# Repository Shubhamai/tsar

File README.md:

# Tsar

This repository contains Tsar flight computer that I have been developing for autonomous vehicles. The goal is to build a general-purpose & fully programmable flight computer that can be used for any autonomous model vehicles. The design is intended to be modular, cost-effective, and easy to manufacture.

The PCB is designed in KiCad and updated to version 8.0.3.

## Version History

### V3 [Latest Version]

The design is very similar to V2 but with different IO style and no pyro channels. The secondary chip is STM32G0 for a lower number of components. The design is still in progress.

#### Key Features:
- Main Dual core ESP32-S3
- Secondary STM32G0 as an IO extender
- 2.4GHz SX1280 radio
- Ublox-M10S GNSS
- BMI088 IMU (up to ± 24 g, ± 2000°/s)
- BMP390 barometer (up to 10KM), MMC5983MA magnetometer for heading
- SD card and flash (ESP32-S3 inbuilt) for data logging & storage
- 14 PWM channels (combined 3A)
- ~20 auxiliary outputs with SPI, I2C, analog, digital pins, etc.
- 6-16V power input, (reverse+over+under)-voltage, over-current protection
- Dimensions: 40mm width, 82mm height

### V2 [April 2024]

With learnings from V1, V2 was designed to be more cost-effective, less complex, and easier to manufacture. The BOM cost was around $60-80, and the board had 4 layers. With a trace width and minimum clearance of 0.2mm, QFN chips, and 0603 components, it was easier to manufacture and assemble. The board was manufactured and partially tested but not yet used in flight.

#### Key Features:
- Main Dual core ESP32-S3
- Secondary RP2040 as an IO extender
- 2.4GHz SX1280 radio
- Ublox-M10S GNSS
- BMI088 IMU (up to ± 24 g, ± 2000°/s)
- BMP390 barometer (up to 10KM), MMC5983MA magnetometer for heading
- 4 pyro channels (up to 16V, 4A) with continuity
- SD card and flash (ESP32-S3 inbuilt) for data logging & storage
- 14 PWM channels (combined 3A)
- 17 auxiliary outputs with SPI, I2C, analog, digital pins, etc.
- 6-16V power input, (reverse+over+under)-voltage, over-current protection
- Dimensions: 40mm width, 82mm height

### V1 [March 2024]

The first attempt at designing a flight computer. The design was powerful, using Teensy, but highly complex and less cost-effective. The BOM cost was around $120-150, and the board had 4 layers. With a trace width and minimum clearance of 0.127mm, BGA chips, and 0402 components, it was challenging to manufacture and assemble. This version was never manufactured or tested.

#### Key Features:
- Main Chip: NXP IMXRT106DVJ6B (Teensy 4.1)
- RP2040 as an IO extender
- 2.4GHz SX1280 radio
- Ublox-M10S GNSS
- BMI088 IMU (up to ± 24 g, ± 2000°/s)
- BMP390 barometer (up to 10KM), MMC5983MA magnetometer for heading
- 4 pyro channels (up to 16V, 4A) with continuity
- SD card and flash for data logging & storage
- 14 PWM channels (combined 3A)
- 30 auxiliary outputs with SPI, I2C, analog, digital pins, etc.
- 6-16V power input, (reverse+over+under)-voltage, over-current protection
- Dimensions: 50mm width, 100mm height

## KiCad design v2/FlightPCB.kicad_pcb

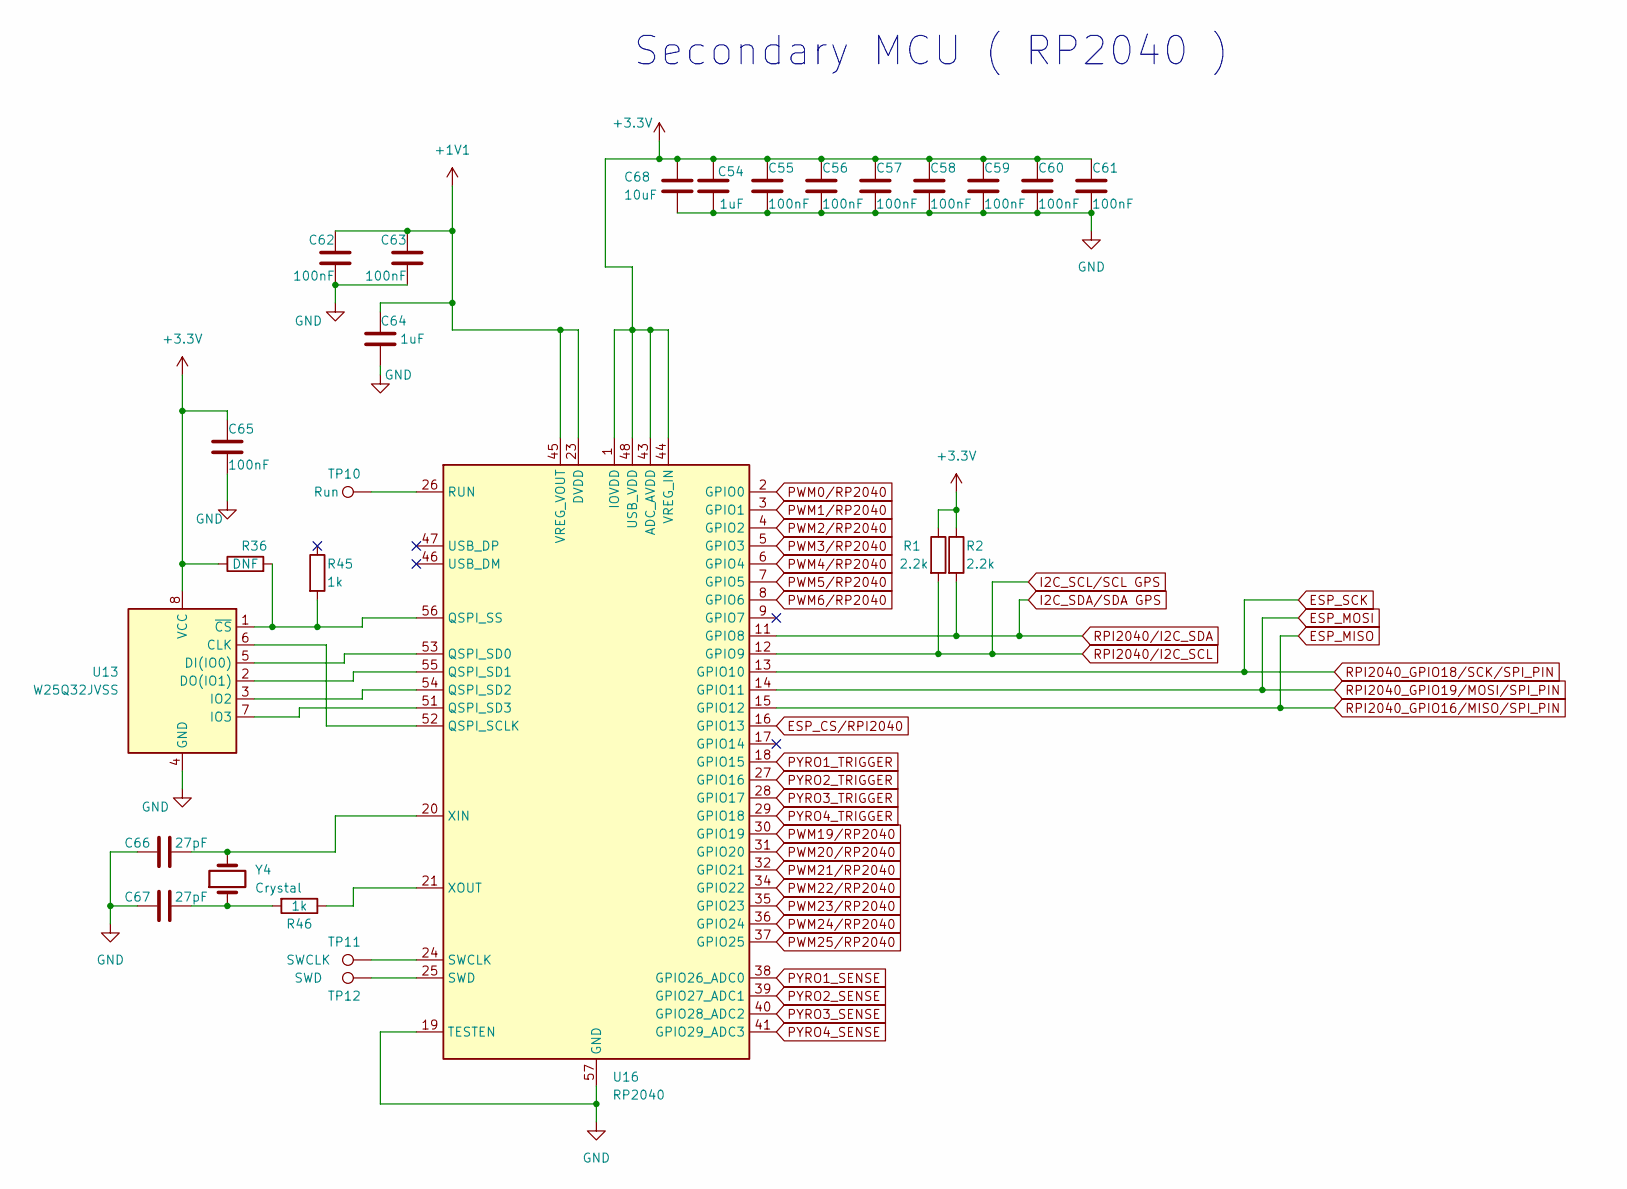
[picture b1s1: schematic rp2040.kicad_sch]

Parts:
C54, C64: 1uF; C_0603_1608Metric
C55, C56, C57, C58, C59, C60, C61, C62, C63, C65: 100nF; C_0603_1608Metric
C66, C67: 27pF; C_0603_1608Metric
C68: 10uF; C_0603_1608Metric
R1, R2: 2.2k; R_0603_1608Metric
R36: DNF; R_0402_1005Metric
R45, R46: 1k; R_0402_1005Metric
TP10: Run; TestPoint_Pad_D1.0mm
TP11: SWCLK; TestPoint_Pad_D2.0mm
TP12: SWD; TestPoint_Pad_D2.0mm
U13: W25Q32JVSS; SOIC-8_5.23x5.23mm_P1.27mm
U16: RP2040; QFN-56-1EP_7x7mm_P0.4mm_EP4x4mm
Y4: Crystal; Crystal_SMD_Abracon_ABM8G-4Pin_3.2x2.5mm

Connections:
+1V1: C62.1, C63.1, C64.1, U16.23 (DVDD), U16.45 (VREG_VOUT), U16.50 (DVDD)
+3.3V: C54.1, C55.1, C56.1, C57.1, C58.1, C59.1, C60.1, C61.1, C65.1, C68.1, R1.1, R2.1, R36.1, U13.8 (VCC), U16.1 (IOVDD), U16.10 (IOVDD), U16.22 (IOVDD), U16.33 (IOVDD), U16.42 (IOVDD), U16.43 (ADC_AVDD), U16.44 (VREG_IN), U16.48 (USB_VDD), U16.49 (IOVDD); also elsewhere on the board
BARO_MISO: U16.15 (GPIO12); also elsewhere on the board
BARO_MOSI: U16.14 (GPIO11); also elsewhere on the board
BARO_SCK: U16.13 (GPIO10); also elsewhere on the board
ESP_CS/RPI2040: U16.16 (GPIO13); also elsewhere on the board
ESP_SCL: R1.2, U16.12 (GPIO9); also elsewhere on the board
ESP_SDA: R2.2, U16.11 (GPIO8); also elsewhere on the board
GND: C54.2, C55.2, C56.2, C57.2, C58.2, C59.2, C60.2, C61.2, C62.2, C63.2, C64.2, C65.2, C66.1, C67.2, C68.2, U13.4 (GND), U16.19 (TESTEN), U16.57 (GND); also elsewhere on the board
unnamed: C67.1, R46.2, Y4.1
unnamed: U13.6 (CLK), U16.52 (QSPI_SCLK)
unnamed: U13.5 (DI(IO0)), U16.53 (QSPI_SD0)
unnamed: U13.2 (DO(IO1)), U16.55 (QSPI_SD1)
unnamed: U13.3 (IO2), U16.54 (QSPI_SD2)
unnamed: U13.7 (IO3), U16.51 (QSPI_SD3)
unnamed: R36.2, R45.2, U13.1 (~CS), U16.56 (QSPI_SS)
unnamed: TP10.1, U16.26 (RUN)
unnamed: TP11.1, U16.24 (SWCLK)
unnamed: TP12.1, U16.25 (SWD)
unnamed: C66.2, U16.20 (XIN), Y4.2
unnamed: R46.1, U16.21 (XOUT)
PWM0/RP2040: U16.2 (GPIO0); also elsewhere on the board
PWM1/RP2040: U16.3 (GPIO1); also elsewhere on the board
PWM2/RP2040: U16.4 (GPIO2); also elsewhere on the board
PWM3/RP2040: U16.5 (GPIO3); also elsewhere on the board
PWM4/RP2040: U16.6 (GPIO4); also elsewhere on the board
PWM5/RP2040: U16.7 (GPIO5); also elsewhere on the board
PWM6/RP2040: U16.8 (GPIO6); also elsewhere on the board
PWM19/RP2040: U16.30 (GPIO19); also elsewhere on the board
PWM20/RP2040: U16.31 (GPIO20); also elsewhere on the board
PWM21/RP2040: U16.32 (GPIO21); also elsewhere on the board
PWM22/RP2040: U16.34 (GPIO22); also elsewhere on the board
PWM23/RP2040: U16.35 (GPIO23); also elsewhere on the board
PWM24/RP2040: U16.36 (GPIO24); also elsewhere on the board
PWM25/RP2040: U16.37 (GPIO25); also elsewhere on the board
PYRO1_SENSE: U16.38 (GPIO26_ADC0); also elsewhere on the board
PYRO1_TRIGGER: U16.18 (GPIO15); also elsewhere on the board
PYRO2_SENSE: U16.39 (GPIO27_ADC1); also elsewhere on the board
PYRO2_TRIGGER: U16.27 (GPIO16); also elsewhere on the board
PYRO3_SENSE: U16.40 (GPIO28_ADC2); also elsewhere on the board
PYRO3_TRIGGER: U16.28 (GPIO17); also elsewhere on the board
PYRO4_SENSE: U16.41 (GPIO29_ADC3); also elsewhere on the board
PYRO4_TRIGGER: U16.29 (GPIO18); also elsewhere on the board

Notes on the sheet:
Secondary MCU ( RP2040 )

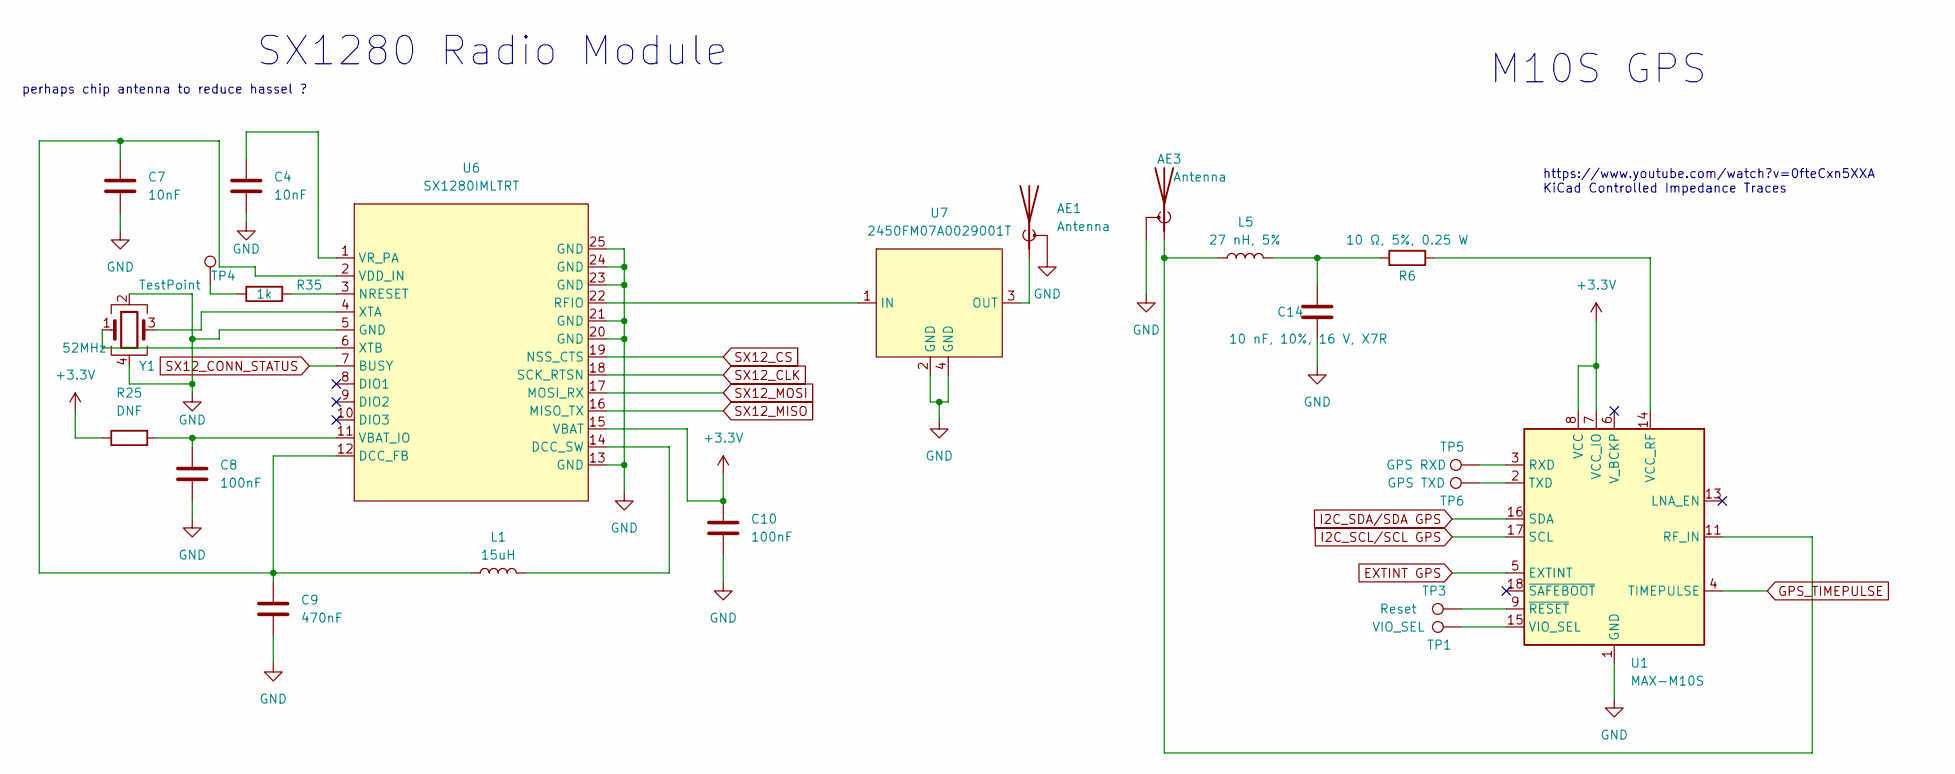
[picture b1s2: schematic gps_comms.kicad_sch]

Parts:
AE1, AE3: Antenna; SMA_Amphenol_901-144_Vertical
C4, C7: 10nF; C_0603_1608Metric
C8, C10: 100nF; C_0603_1608Metric
C9: 470nF; C_0402_1005Metric
C14: 10 nF, 10%, 16 V, X7R; C_0603_1608Metric
L1: 15uH; L_0805_2012Metric
L5: 27 nH, 5%; L_0402_1005Metric
R6: 10 Ω, 5%, 0.25 W; R_0402_1005Metric
R25: DNF; R_0402_1005Metric
R35: 1k; R_0402_1005Metric
TP1: VIO_SEL; TestPoint_Pad_D1.0mm
TP3: Reset; TestPoint_Pad_D1.0mm
TP4: TestPoint; TestPoint_Pad_D1.0mm
TP5: GPS RXD; TestPoint_Pad_D1.0mm
TP6: GPS TXD; TestPoint_Pad_D1.0mm
U1: MAX-M10S; ublox_MAX
U6: SX1280IMLTRT; QFN-24-1EP_4x4mm_P0.5mm_EP2.7x2.7mm
U7: 2450FM07A0029001T
Y1: 52MHz; Crystal_SMD_2016-4Pin_2.0x1.6mm

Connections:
+3.3V: C10.1, R25.1, U1.7 (VCC_IO), U1.8 (VCC), U6.15 (VBAT); also elsewhere on the board
BARO_MISO: U6.16 (MISO_TX); also elsewhere on the board
BARO_MOSI: U6.17 (MOSI_RX); also elsewhere on the board
BARO_SCK: U6.18 (SCK_RTSN); also elsewhere on the board
ESP_SCL: U1.17 (SCL); also elsewhere on the board
ESP_SDA: U1.16 (SDA); also elsewhere on the board
EXTINT GPS: U1.5 (EXTINT); also elsewhere on the board
GND: AE1.2 (Shield), AE3.2 (Shield), C4.2, C7.2, C8.2, C9.2, C10.2, C14.1, U1.1 (GND), U1.10 (GND), U1.12 (GND), U6.5 (GND), U6.13 (GND), U6.20 (GND), U6.21 (GND), U6.23 (GND), U6.24 (GND), U6.25 (GND), U7.2 (GND), U7.4 (GND), Y1.2, Y1.4; also elsewhere on the board
GPS_TIMEPULSE: U1.4 (TIMEPULSE); also elsewhere on the board
unnamed: AE1.1 (A), U7.3 (OUT)
unnamed: AE3.1 (A), L5.1, U1.11 (RF_IN)
unnamed: C14.2, L5.2, R6.1
unnamed: R35.1, TP4.1
unnamed: TP5.1, U1.3 (RXD)
unnamed: TP6.1, U1.2 (TXD)
unnamed: R6.2, U1.14 (VCC_RF)
unnamed: TP1.1, U1.15 (VIO_SEL)
unnamed: TP3.1, U1.9 (~RESET)
unnamed: C7.1, C9.1, L1.1, U6.2 (VDD_IN), U6.12 (DCC_FB)
unnamed: L1.2, U6.14 (DCC_SW)
unnamed: R35.2, U6.3 (NRESET)
unnamed: U6.22 (RFIO), U7.1 (IN)
unnamed: C8.1, R25.2, U6.11 (VBAT_IO)
unnamed: C4.1, U6.1 (VR_PA)
unnamed: U6.4 (XTA), Y1.3
unnamed: U6.6 (XTB), Y1.1
SX12_CONN_STATUS: U6.7 (BUSY); also elsewhere on the board
SX12_CS: U6.19 (NSS_CTS); also elsewhere on the board

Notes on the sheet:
perhaps chip antenna to reduce hassel ?
https://www.youtube.com/watch?v=0fteCxn5XXA KiCad Controlled Impedance Traces
M10S GPS
SX1280 Radio Module

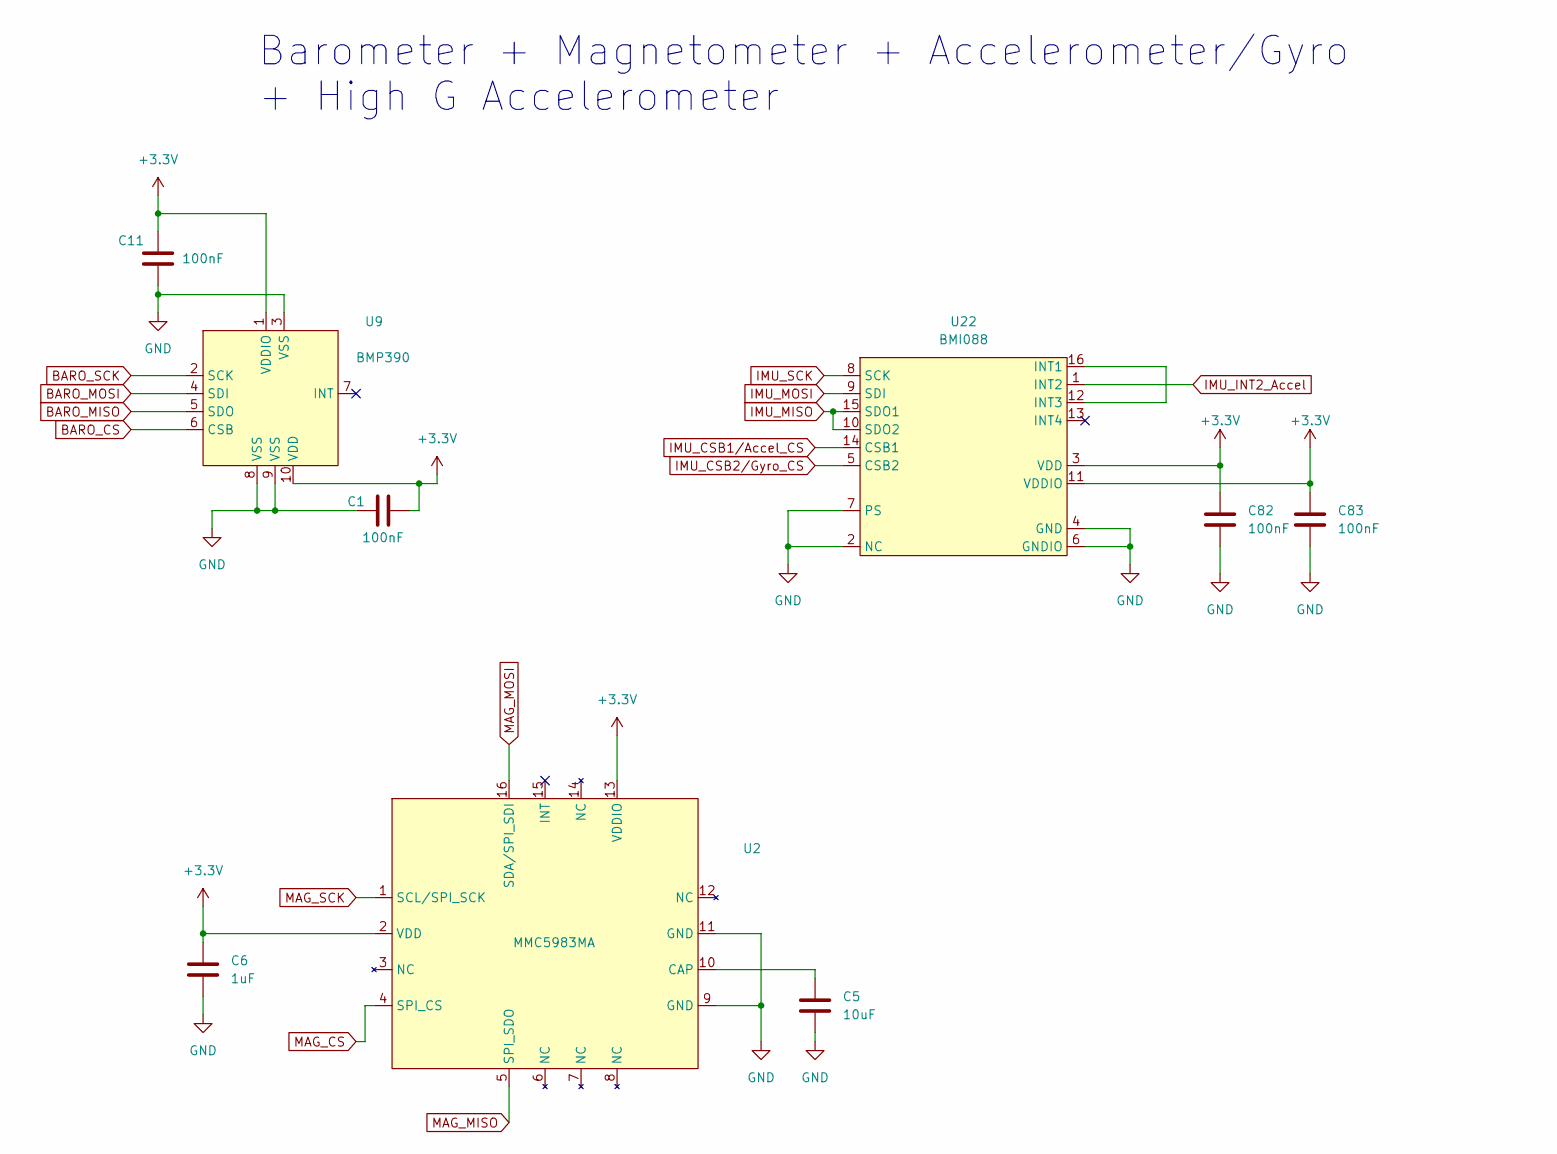
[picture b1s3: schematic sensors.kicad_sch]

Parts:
C1, C11, C82, C83: 100nF; C_0603_1608Metric
C5: 10uF; C_0603_1608Metric
C6: 1uF; C_0603_1608Metric
U2: MMC5983MA
U9: BMP390
U22: BMI088

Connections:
+3.3V: C1.2, C6.1, C11.2, C82.1, C83.1, U2.2 (VDD), U2.13 (VDDIO), U9.1 (VDDIO), U9.10 (VDD), U22.3 (VDD), U22.11 (VDDIO); also elsewhere on the board
BARO_CS: U9.6 (CSB); also elsewhere on the board
BARO_MISO: U2.5 (SPI_SDO), U9.5 (SDO), U22.10 (SDO2), U22.15 (SDO1); also elsewhere on the board
BARO_MOSI: U2.16 (SDA/SPI_SDI), U9.4 (SDI), U22.9 (SDI); also elsewhere on the board
BARO_SCK: U2.1 (SCL/SPI_SCK), U9.2 (SCK), U22.8 (SCK); also elsewhere on the board
GND: C1.1, C5.2, C6.2, C11.1, C82.2, C83.2, U2.9 (GND), U2.11 (GND), U9.3 (VSS), U9.8 (VSS), U9.9 (VSS), U22.2 (NC), U22.4 (GND), U22.6 (GNDIO), U22.7 (PS); also elsewhere on the board
IMU_CSB1/Accel_CS: U22.14 (CSB1); also elsewhere on the board
IMU_CSB2/Gyro_CS: U22.5 (CSB2); also elsewhere on the board
IMU_INT2_Accel: U22.1 (INT2); also elsewhere on the board
MAG_CS: U2.4 (SPI_CS); also elsewhere on the board
unnamed: C5.1, U2.10 (CAP)
unnamed: U22.12 (INT3), U22.16 (INT1)

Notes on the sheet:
Barometer + Magnetometer + Accelerometer/Gyro + High G Accelerometer

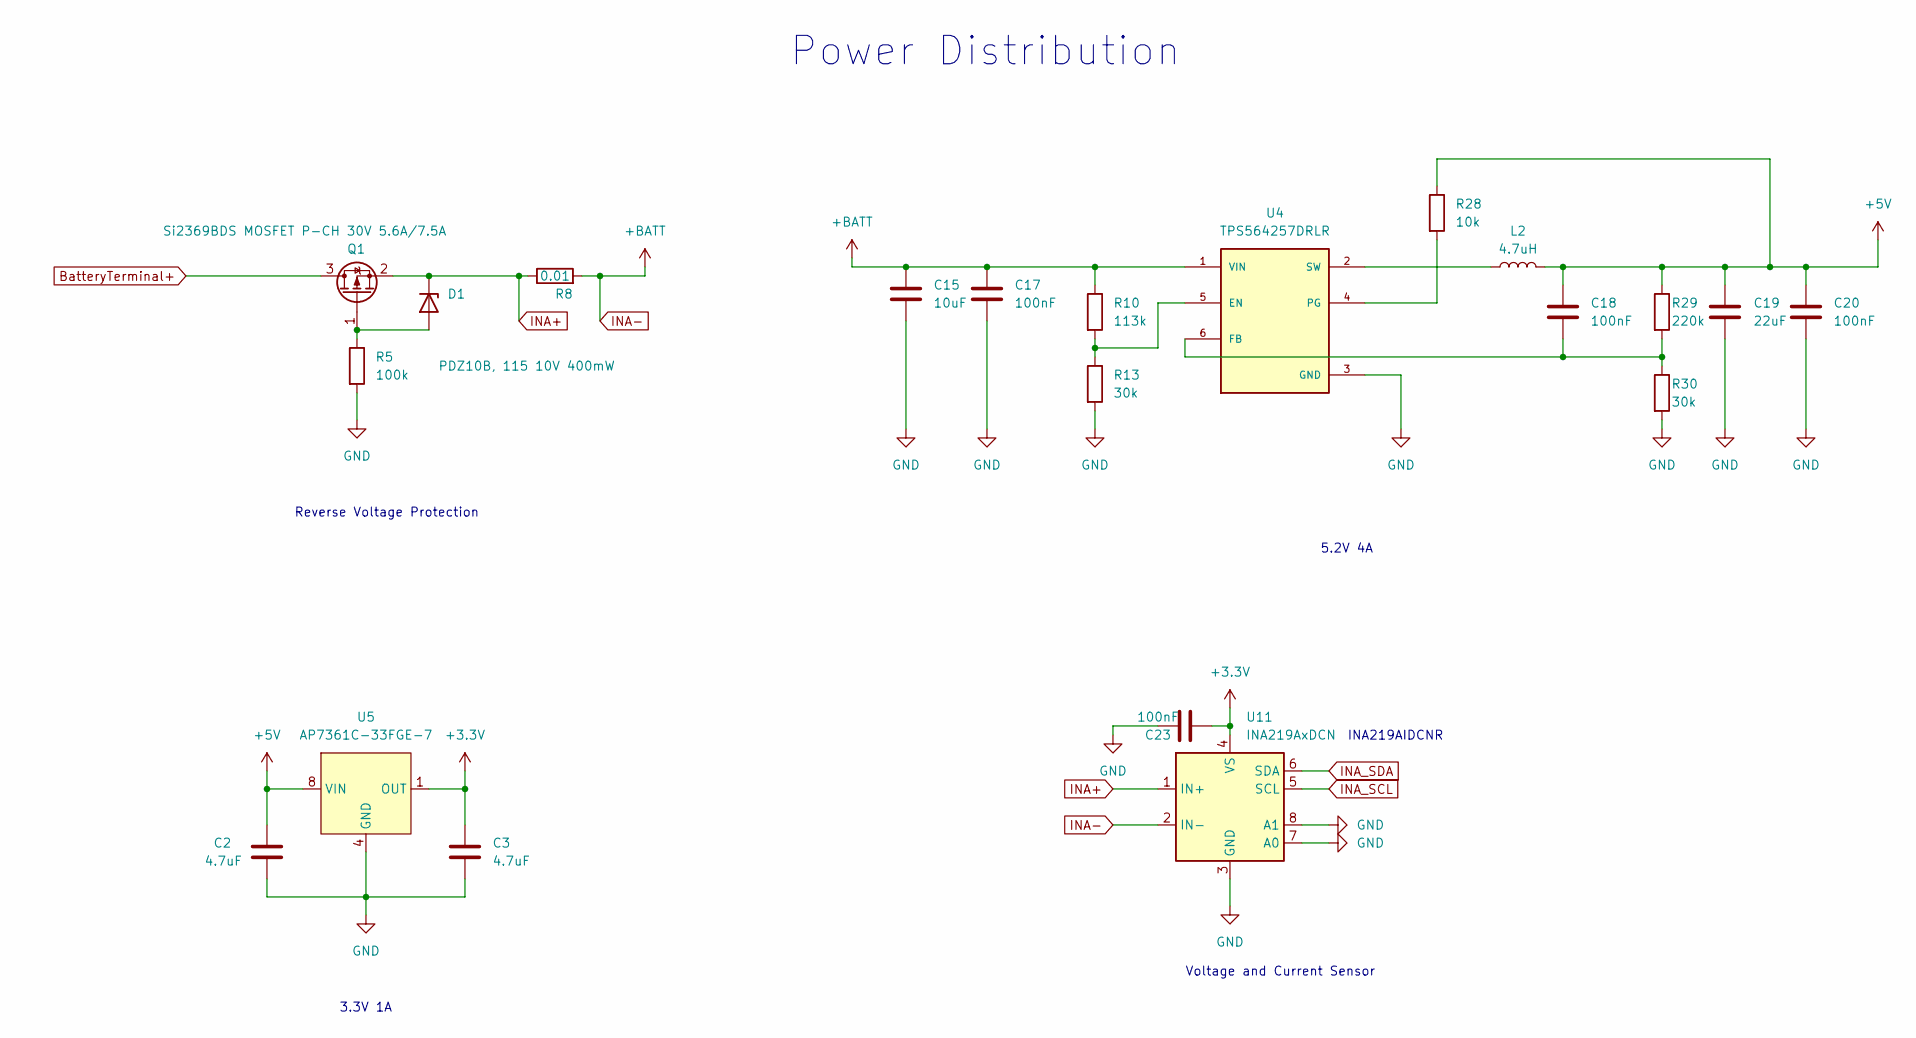
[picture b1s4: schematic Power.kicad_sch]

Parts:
C2, C3: 4.7uF; C_0603_1608Metric
C15: 10uF; C_0603_1608Metric
C17, C18, C20, C23: 100nF; C_0603_1608Metric
C19: 22uF; C_0805_2012Metric
D1: PDZ10B, 115 10V 400mW; D_0805_2012Metric
L2: 4.7uH; L_Cenker_CKCS8040
Q1: Si2369BDS MOSFET P-CH 30V 5.6A/7.5A; SOT-23
R5: 100k; R_0805_2012Metric
R8: 0.01; R_2512_6332Metric
R10: 113k; R_0603_1608Metric
R13, R30: 30k; R_0603_1608Metric
R28: 10k; R_0603_1608Metric
R29: 220k; R_0603_1608Metric
U4: TPS564257DRLR; SOT50P160X60-6N; PARTREV A
U5: AP7361C-33FGE-7; MLF-8-1EP_3x3mm_P0.65mm_EP1.55x2.3mm
U11: INA219AxDCN; SOT-23-8

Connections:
+3.3V: C3.1, C23.2, U5.1 (OUT), U11.4 (VS); also elsewhere on the board
BatteryTerminal+: Q1.3 (D); also elsewhere on the board
ESP_SCL: U11.5 (SCL); also elsewhere on the board
ESP_SDA: U11.6 (SDA); also elsewhere on the board
GND: C2.2, C3.2, C15.2, C17.2, C19.2, C20.2, C23.1, R5.2, R13.2, R30.2, U4.3 (GND), U5.4 (GND), U11.3 (GND), U11.7 (A0), U11.8 (A1); also elsewhere on the board
INA+: D1.1 (K), Q1.2 (S), R8.1, U11.1 (IN+)
INA-: C15.1, C17.1, R8.2, R10.1, U4.1 (VIN), U11.2 (IN-); also elsewhere on the board
unnamed: D1.2 (A), Q1.1 (G), R5.1
unnamed: R10.2, R13.1, U4.5 (EN)
unnamed: C18.2, R29.2, R30.1, U4.6 (FB)
unnamed: R28.2, U4.4 (PG)
unnamed: L2.1, U4.2 (SW)

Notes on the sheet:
INA219AIDCNR
Voltage and Current Sensor
3.3V 1A
Reverse Voltage Protection
5.2V 4A
Power Distribution

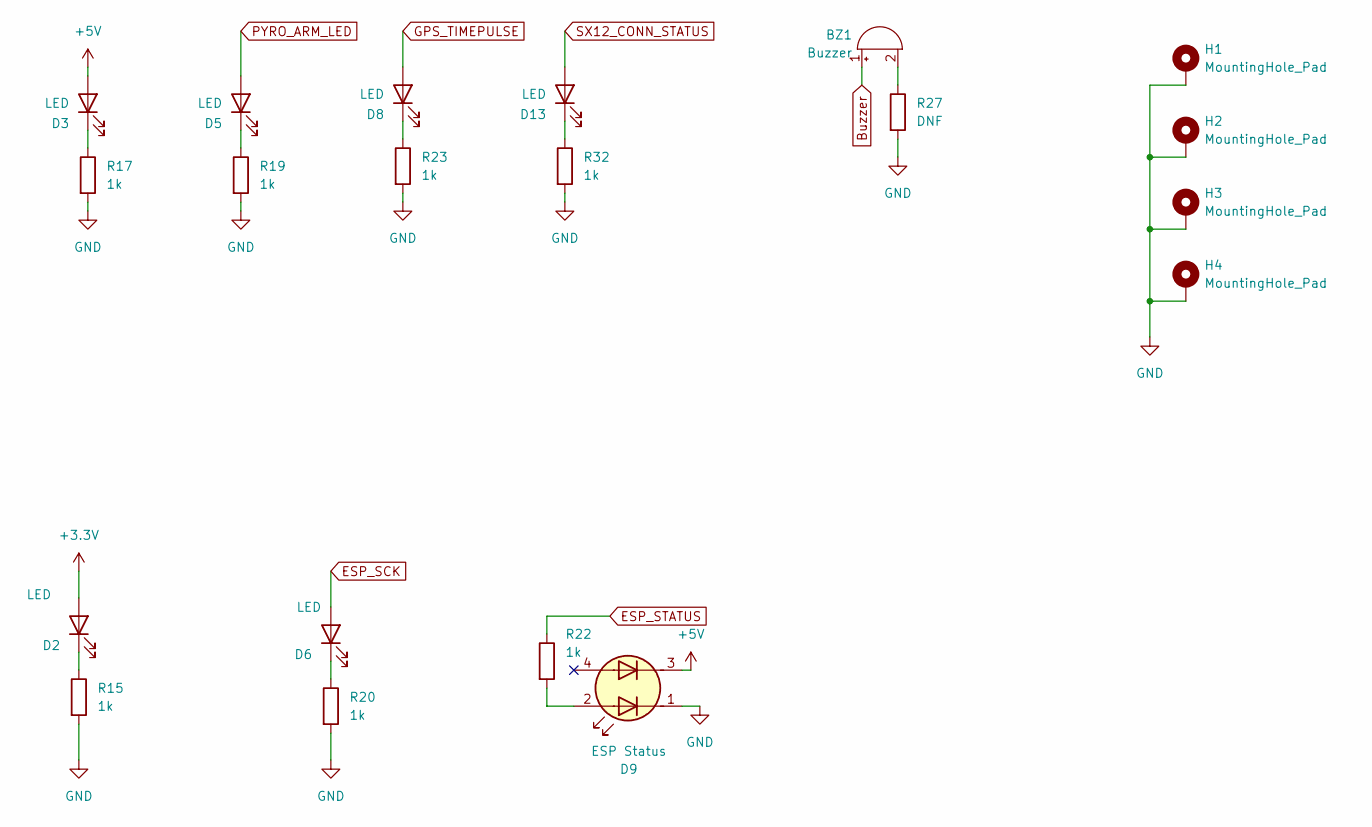
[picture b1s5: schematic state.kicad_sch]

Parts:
BZ1: Buzzer; Buzzer_CUI_CPT-9019S-SMT
D2, D3, D5, D6, D8, D13: LED; LED_0402_1005Metric
D9: ESP Status; IN-PI22TAT5R5G5B
H1, H2, H3, H4: MountingHole_Pad; MountingHole_2.7mm_M2.5_Pad_Via
R15, R17, R19, R20, R22, R23, R32: 1k; R_0402_1005Metric
R27: DNF; R_0402_1005Metric

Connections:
+3.3V: D2.2 (A); also elsewhere on the board
BARO_SCK: D6.2 (A); also elsewhere on the board
Buzzer: BZ1.1 (+); also elsewhere on the board
ESP_STATUS: R22.1; also elsewhere on the board
GND: D9.1 (A1), H1.1, H2.1, H3.1, H4.1, R15.2, R17.2, R19.2, R20.2, R23.2, R27.2, R32.2; also elsewhere on the board
GPS_TIMEPULSE: D8.2 (A); also elsewhere on the board
unnamed: BZ1.2 (-), R27.1
unnamed: D2.1 (K), R15.1
unnamed: D3.1 (K), R17.1
unnamed: D5.1 (K), R19.1
unnamed: D6.1 (K), R20.1
unnamed: D8.1 (K), R23.1
unnamed: D9.2 (K1), R22.2
unnamed: D13.1 (K), R32.1
PYRO_ARM_LED: D5.2 (A); also elsewhere on the board
SX12_CONN_STATUS: D13.2 (A); also elsewhere on the board

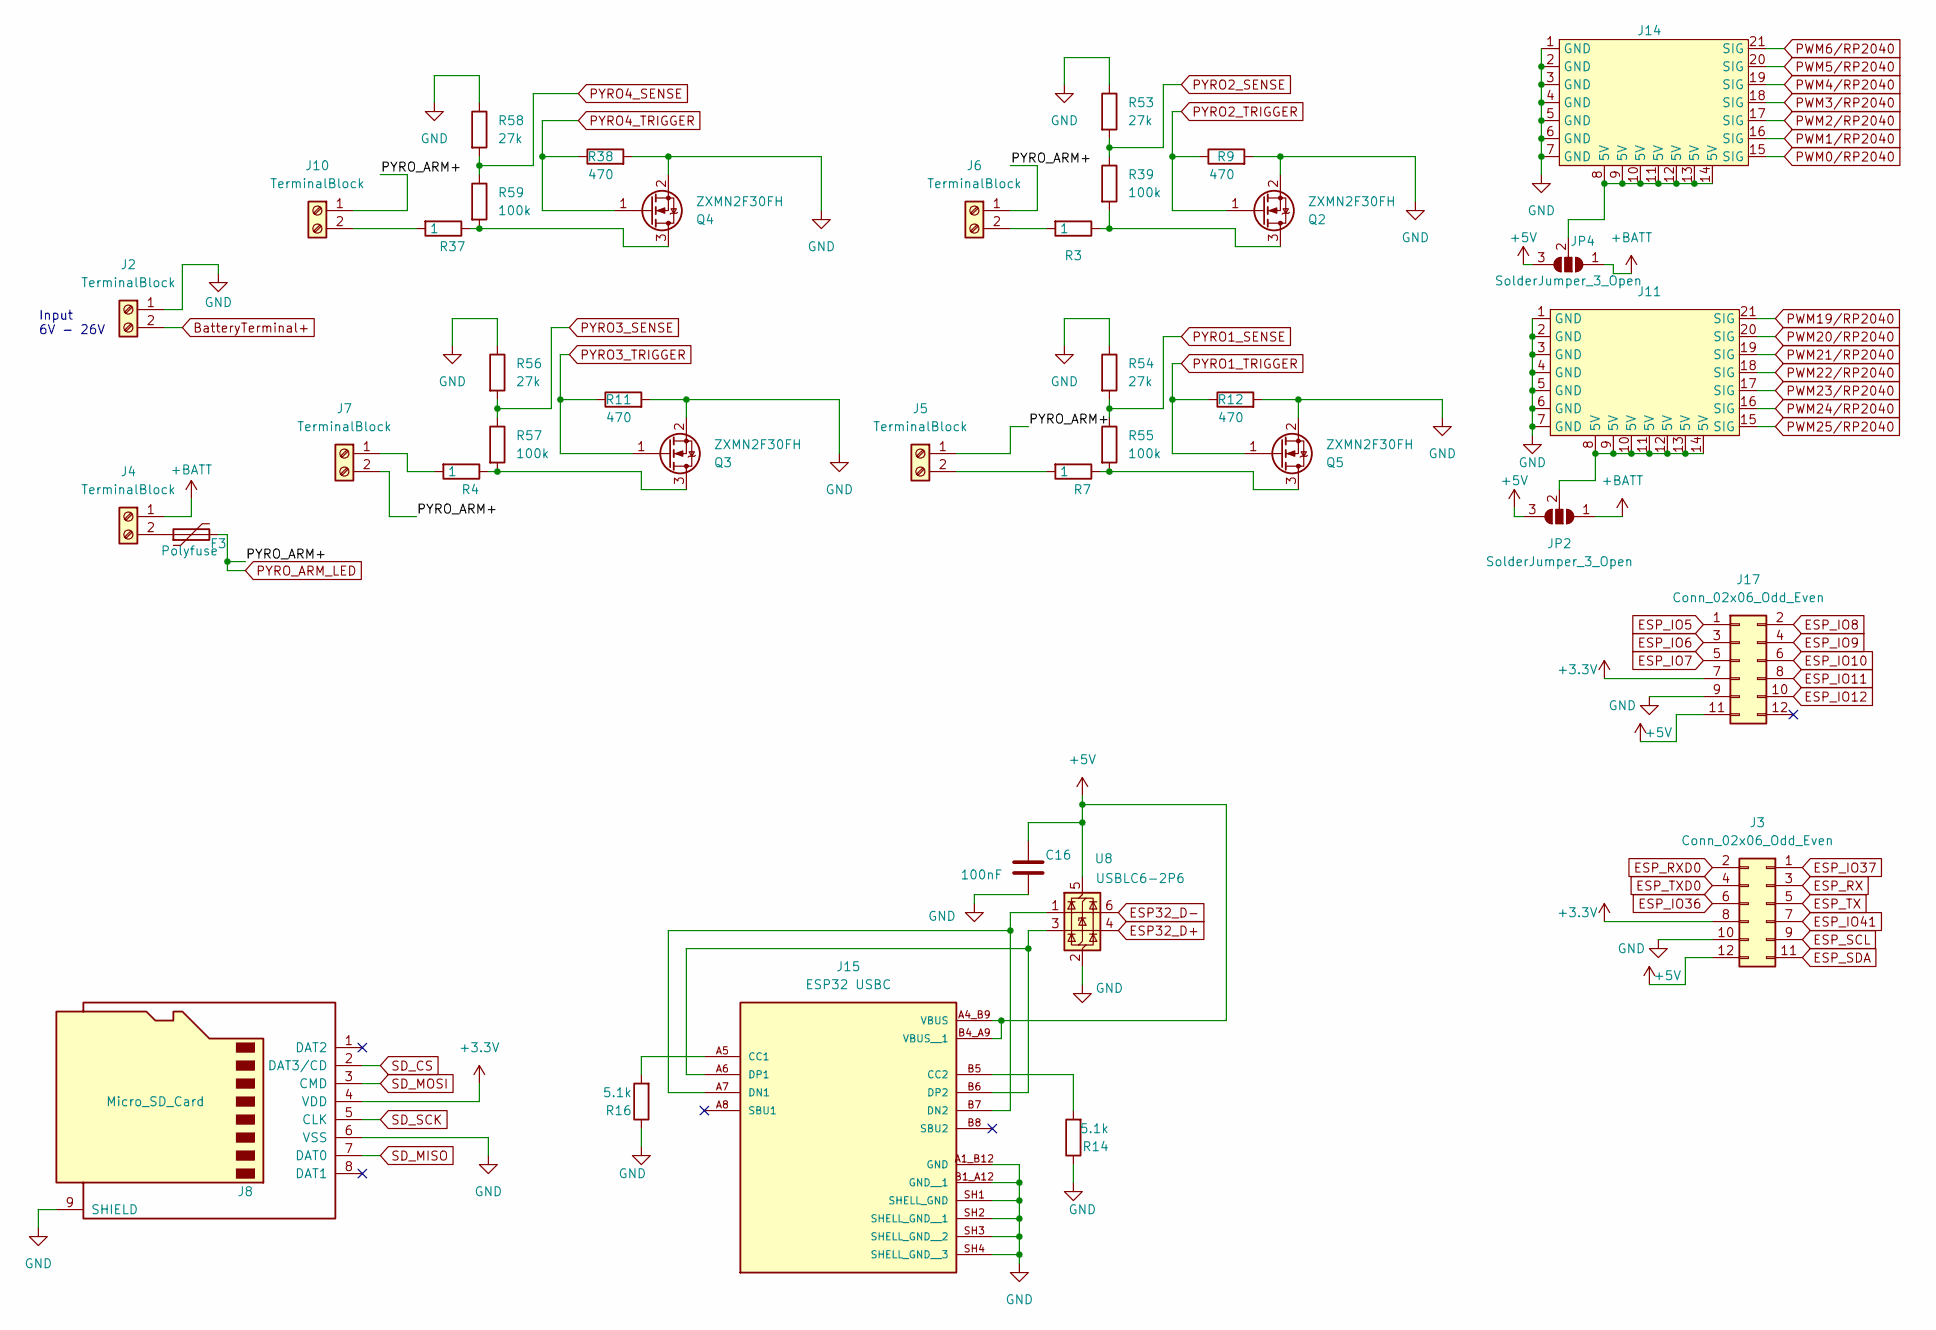
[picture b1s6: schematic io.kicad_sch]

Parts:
C16: 100nF; C_0603_1608Metric
F3: Polyfuse; Fuse_1812_4532Metric
J2, J4, J5, J6, J7, J10: TerminalBlock; TerminalBlock_Phoenix_PT-1,5-2-5.0-H_1x02_P5.00mm_Horizontal
J3, J17: Conn_02x06_Odd_Even; PinSocket_2x06_P2.54mm_Vertical
J8: Micro_SD_Card; microSD_HC_Molex_47219-2001
J11: PinHeader_3x05_P2.54mm_Vertical_Left
J14: PinHeader_3x05_P2.54mm_Vertical_Right
J15: ESP32 USBC; GCT_USB4105-GF-A; PARTREV B3
JP2, JP4: SolderJumper_3_Open; SolderJumper-3_P2.0mm_Open_TrianglePad1.0x1.5mm
Q2, Q3, Q4, Q5: ZXMN2F30FH; SOT-23
R3, R4, R7, R37: 1; R_0603_1608Metric
R9, R11, R12, R38: 470; R_0603_1608Metric
R14, R16: 5.1k; R_0603_1608Metric
R39, R55, R57, R59: 100k; R_0805_2012Metric
R53, R54, R56, R58: 27k; R_0603_1608Metric
U8: USBLC6-2P6; SOT-666

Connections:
+3.3V: J3.8, J8.4 (VDD), J17.7; also elsewhere on the board
BARO_MISO: J8.7 (DAT0); also elsewhere on the board
BARO_MOSI: J8.3 (CMD); also elsewhere on the board
BARO_SCK: J8.5 (CLK); also elsewhere on the board
BatteryTerminal+: J2.2; also elsewhere on the board
ESP32_D+: U8.4 (I/O2); also elsewhere on the board
ESP32_D-: U8.6 (I/O1); also elsewhere on the board
ESP_IO5: J17.1; also elsewhere on the board
ESP_IO6: J17.3; also elsewhere on the board
ESP_IO7: J17.5; also elsewhere on the board
ESP_IO8: J17.2; also elsewhere on the board
ESP_IO9: J17.4; also elsewhere on the board
ESP_IO10: J17.6; also elsewhere on the board
ESP_IO11: J17.8; also elsewhere on the board
ESP_IO12: J17.10; also elsewhere on the board
ESP_IO36: J3.6; also elsewhere on the board
ESP_IO37: J3.1; also elsewhere on the board
ESP_IO41: J3.7; also elsewhere on the board
ESP_RX: J3.3; also elsewhere on the board
ESP_RXD0: J3.2; also elsewhere on the board
ESP_SCL: J3.9; also elsewhere on the board
ESP_SDA: J3.11; also elsewhere on the board
ESP_TX: J3.5; also elsewhere on the board
ESP_TXD0: J3.4; also elsewhere on the board
GND: C16.2, J2.1, J3.10, J8.6 (VSS), J8.9 (SHIELD), J11.1 (GND), J11.2 (GND), J11.3 (GND), J11.4 (GND), J11.5 (GND), J11.6 (GND), J11.7 (GND), J14.1 (GND), J14.2 (GND), J14.3 (GND), J14.4 (GND), J14.5 (GND), J14.6 (GND), J14.7 (GND), J15.A1_B12 (GND), J15.B1_A12 (GND__1), J15.SH1 (SHELL_GND), J15.SH2 (SHELL_GND__1), J15.SH3 (SHELL_GND__2), J15.SH4 (SHELL_GND__3), J17.9, Q2.2 (S), Q3.2 (S), Q4.2 (S), Q5.2 (S), R9.2, R11.2, R12.2, R14.1, R16.1, R38.2, R53.1, R54.1, R56.1, R58.1, U8.2 (GND); also elsewhere on the board
INA-: J4.1, JP2.1 (A), JP4.1 (A); also elsewhere on the board
unnamed: F3.1, J4.2
unnamed: J5.2, R7.2
unnamed: J6.2, R3.2
unnamed: J7.1, R4.2
unnamed: J10.2, R37.2
unnamed: J15.A5 (CC1), R16.2
unnamed: J15.B5 (CC2), R14.2
unnamed: J15.A7 (DN1), J15.B7 (DN2), U8.1 (I/O1)
unnamed: J15.A6 (DP1), J15.B6 (DP2), U8.3 (I/O2)
unnamed: Q2.3 (D), R3.1, R39.2
unnamed: Q3.3 (D), R4.1, R57.2
unnamed: Q4.3 (D), R37.1, R59.2
unnamed: Q5.3 (D), R7.1, R55.2
PWM0/RP2040: J14.15 (SIG); also elsewhere on the board
PWM1/RP2040: J14.16 (SIG); also elsewhere on the board
PWM2/RP2040: J14.17 (SIG); also elsewhere on the board
PWM3/RP2040: J14.18 (SIG); also elsewhere on the board
PWM4/RP2040: J14.19 (SIG); also elsewhere on the board
PWM5/RP2040: J14.20 (SIG); also elsewhere on the board
PWM6/RP2040: J14.21 (SIG); also elsewhere on the board
PWM19/RP2040: J11.21 (SIG); also elsewhere on the board
PWM20/RP2040: J11.20 (SIG); also elsewhere on the board
PWM21/RP2040: J11.19 (SIG); also elsewhere on the board
PWM22/RP2040: J11.18 (SIG); also elsewhere on the board
PWM23/RP2040: J11.17 (SIG); also elsewhere on the board
PWM24/RP2040: J11.16 (SIG); also elsewhere on the board
PWM25/RP2040: J11.15 (SIG); also elsewhere on the board
PYRO1_SENSE: R54.2, R55.1; also elsewhere on the board
PYRO1_TRIGGER: Q5.1 (G), R12.1; also elsewhere on the board
PYRO2_SENSE: R39.1, R53.2; also elsewhere on the board
PYRO2_TRIGGER: Q2.1 (G), R9.1; also elsewhere on the board
PYRO3_SENSE: R56.2, R57.1; also elsewhere on the board
PYRO3_TRIGGER: Q3.1 (G), R11.1; also elsewhere on the board
PYRO4_SENSE: R58.2, R59.1; also elsewhere on the board
PYRO4_TRIGGER: Q4.1 (G), R38.1; also elsewhere on the board
PYRO_ARM_LED: F3.2, J5.1, J6.1, J7.2, J10.1; also elsewhere on the board
SD_CS: J8.2 (DAT3/CD); also elsewhere on the board

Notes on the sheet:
Input 6V - 26V

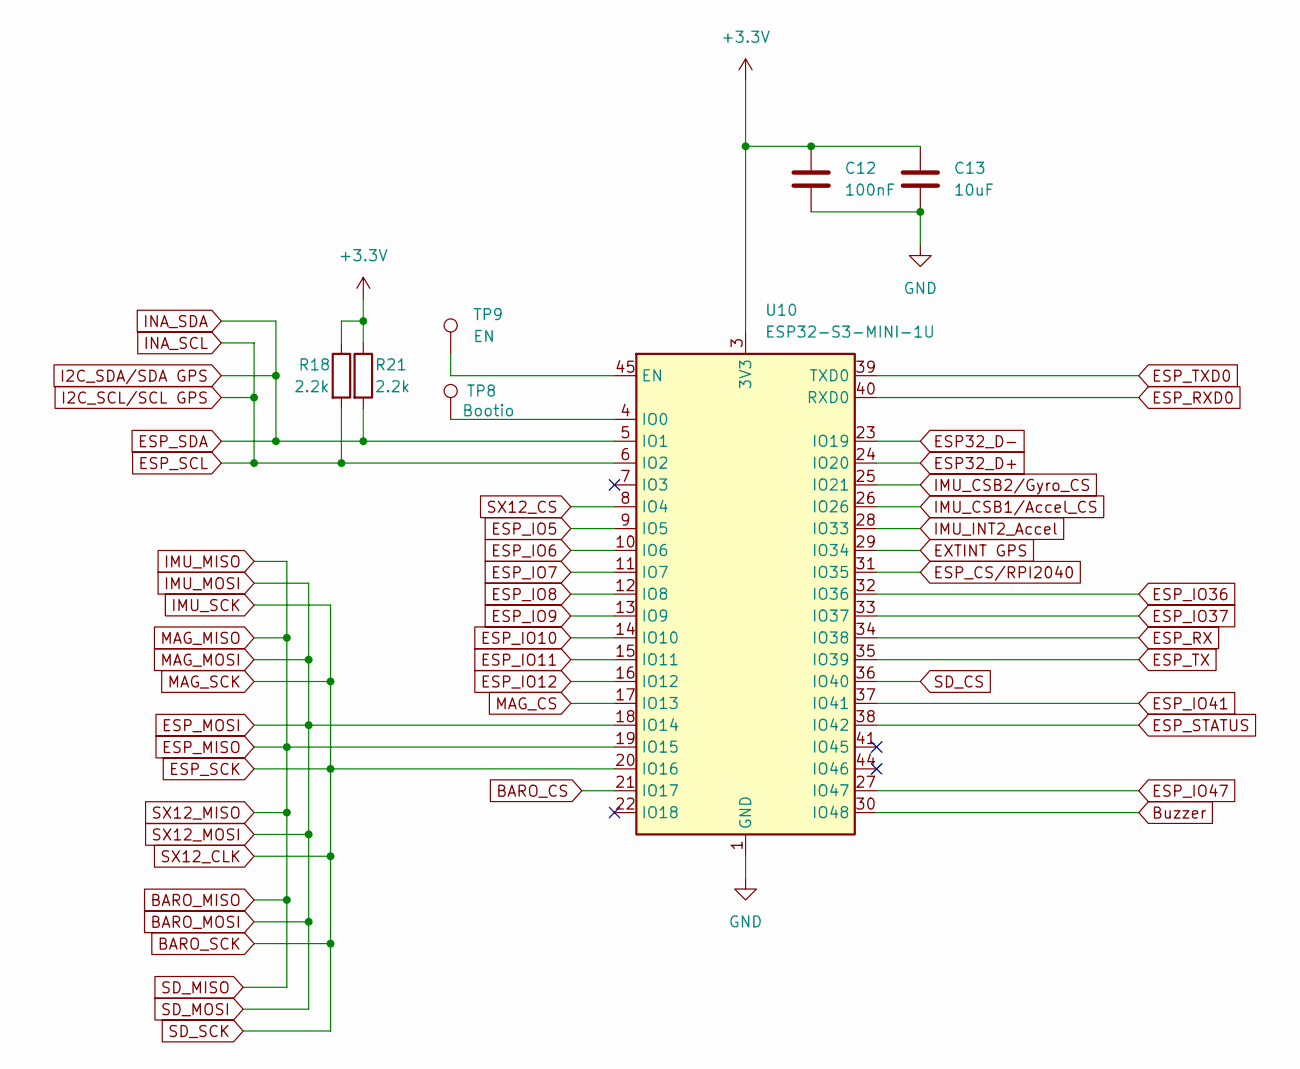
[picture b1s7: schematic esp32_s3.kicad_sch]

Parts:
C12: 100nF; C_0603_1608Metric
C13: 10uF; C_0603_1608Metric
R18, R21: 2.2k; R_0603_1608Metric
TP8: Bootio; TestPoint_Pad_D1.0mm
TP9: EN; TestPoint_Pad_D1.0mm
U10: ESP32-S3-MINI-1U; ESP32-S2-MINI-1U

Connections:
+3.3V: C12.1, C13.1, R18.1, R21.1, U10.3 (3V3); also elsewhere on the board
BARO_CS: U10.21 (IO17); also elsewhere on the board
BARO_MISO: U10.19 (IO15); also elsewhere on the board
BARO_MOSI: U10.18 (IO14); also elsewhere on the board
BARO_SCK: U10.20 (IO16); also elsewhere on the board
Buzzer: U10.30 (IO48); also elsewhere on the board
ESP32_D+: U10.24 (IO20); also elsewhere on the board
ESP32_D-: U10.23 (IO19); also elsewhere on the board
ESP_CS/RPI2040: U10.31 (IO35); also elsewhere on the board
ESP_IO5: U10.9 (IO5); also elsewhere on the board
ESP_IO6: U10.10 (IO6); also elsewhere on the board
ESP_IO7: U10.11 (IO7); also elsewhere on the board
ESP_IO8: U10.12 (IO8); also elsewhere on the board
ESP_IO9: U10.13 (IO9); also elsewhere on the board
ESP_IO10: U10.14 (IO10); also elsewhere on the board
ESP_IO11: U10.15 (IO11); also elsewhere on the board
ESP_IO12: U10.16 (IO12); also elsewhere on the board
ESP_IO36: U10.32 (IO36); also elsewhere on the board
ESP_IO37: U10.33 (IO37); also elsewhere on the board
ESP_IO41: U10.37 (IO41); also elsewhere on the board
ESP_IO47: U10.27 (IO47)
ESP_RX: U10.34 (IO38); also elsewhere on the board
ESP_RXD0: U10.40 (RXD0); also elsewhere on the board
ESP_SCL: R18.2, U10.6 (IO2); also elsewhere on the board
ESP_SDA: R21.2, U10.5 (IO1); also elsewhere on the board
ESP_STATUS: U10.38 (IO42); also elsewhere on the board
ESP_TX: U10.35 (IO39); also elsewhere on the board
ESP_TXD0: U10.39 (TXD0); also elsewhere on the board
EXTINT GPS: U10.29 (IO34); also elsewhere on the board
GND: C12.2, C13.2, U10.1 (GND), U10.2 (GND), U10.42 (GND), U10.43 (GND), U10.46 (GND), U10.47 (GND), U10.48 (GND), U10.49 (GND), U10.50 (GND), U10.51 (GND), U10.52 (GND), U10.53 (GND), U10.54 (GND), U10.55 (GND), U10.56 (GND), U10.57 (GND), U10.58 (GND), U10.59 (GND), U10.60 (GND), U10.61 (GND), U10.62 (GND), U10.63 (GND), U10.64 (GND), U10.65 (GND); also elsewhere on the board
IMU_CSB1/Accel_CS: U10.26 (IO26); also elsewhere on the board
IMU_CSB2/Gyro_CS: U10.25 (IO21); also elsewhere on the board
IMU_INT2_Accel: U10.28 (IO33); also elsewhere on the board
MAG_CS: U10.17 (IO13); also elsewhere on the board
unnamed: TP9.1, U10.45 (EN)
unnamed: TP8.1, U10.4 (IO0)
SD_CS: U10.36 (IO40); also elsewhere on the board
SX12_CS: U10.8 (IO4); also elsewhere on the board

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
